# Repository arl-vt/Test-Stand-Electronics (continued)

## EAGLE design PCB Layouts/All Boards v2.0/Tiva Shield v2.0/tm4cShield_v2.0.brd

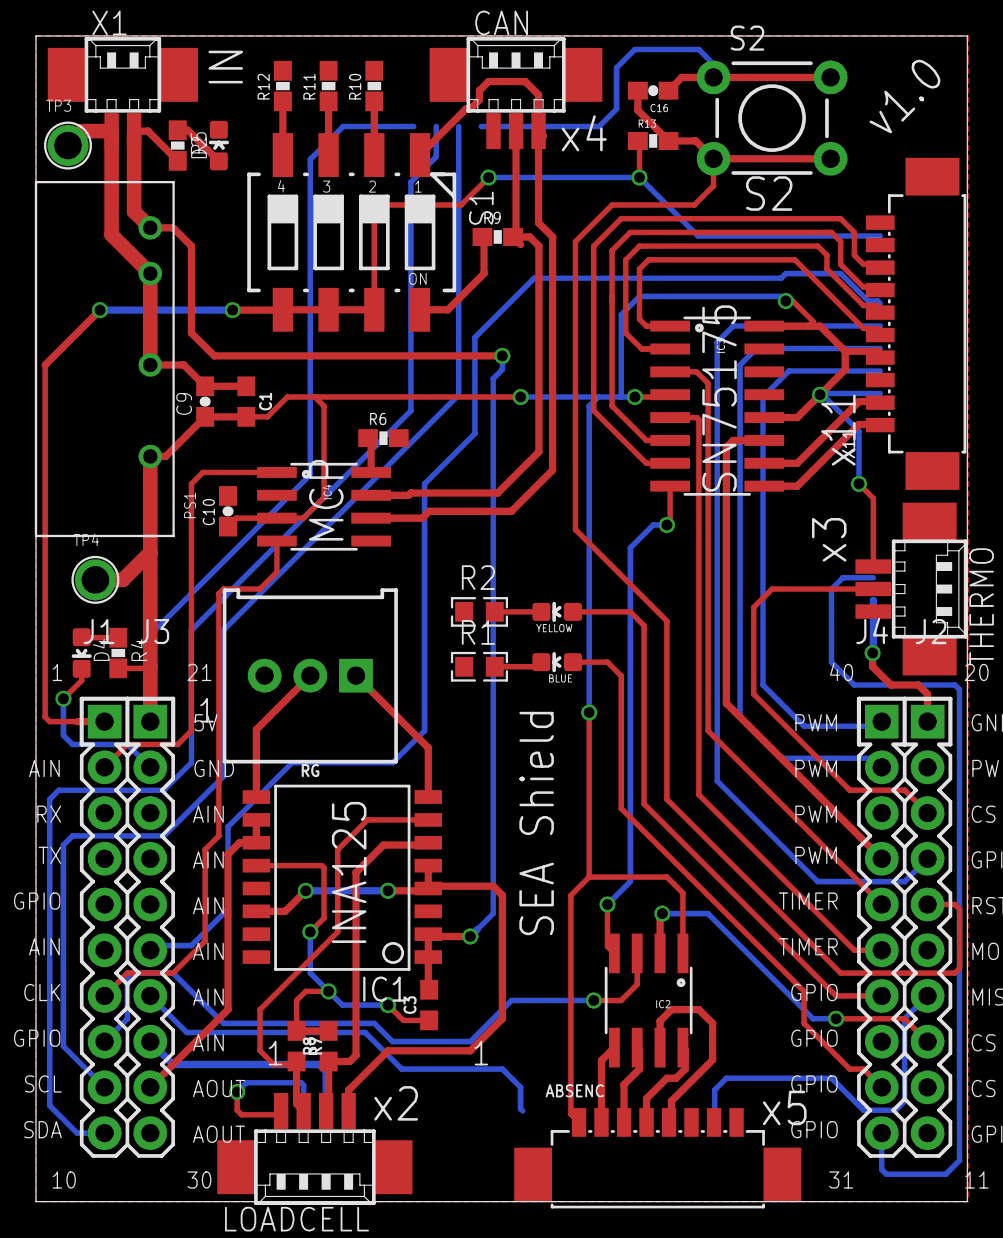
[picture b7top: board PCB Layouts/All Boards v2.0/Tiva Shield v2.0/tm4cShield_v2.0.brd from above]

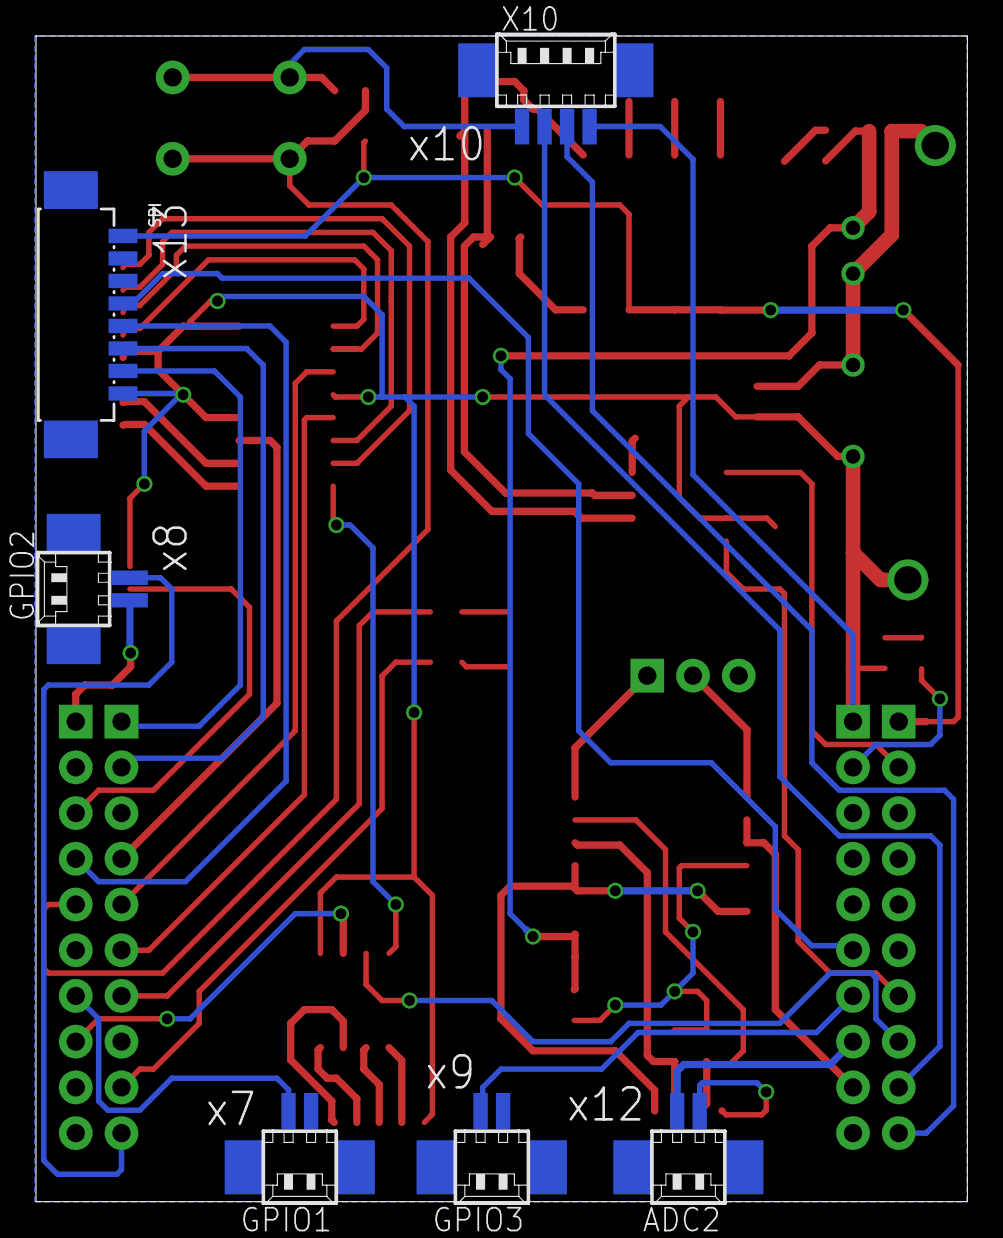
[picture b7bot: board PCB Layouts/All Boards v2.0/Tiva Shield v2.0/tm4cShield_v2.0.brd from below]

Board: 2 copper layers, 51.7 x 64.8 mm, 44 parts (6 on the bottom side), 52 nets.

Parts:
A1: 4X10-BOOSTERPACK
ABSENC: x5; PB-53261-08
ADC2: x12; 53261-02
BLUE: LED-0603
C1, C3: 0.1uF; 0603
C9: 2.2u; 0603-CAP
C10, C16: 100nF; 0603-CAP
CAN: x4; 53261-03
D2: 12V; LED-0603
D4: 5V; LED-0603
GPIO1: x7; 53261-02
GPIO2: x8; 53261-02
GPIO3: x9; 53261-02
IC1: INA125U; SO16-1
IC2: SP490; SOIC8
IC3: SN75175; SOIC16
IC4: MCP2551; SOIC8
LOADCELL: x2; 53261-04
PS1: 12/5; MURATA_NMG
R1, R2: RESC0603
R4: 1k; 0603-RES
R5: 4k7; 0603-RES
R6: 4.7K; 0603-RES
R7, R8: 10k; 0603
R9: 120; 0603-RES
R10, R11, R12, R13: 10K; 0603-RES
RG: 10k; TRIMPOT-PTH-3386U
S1: 219-04; CTS-219-04
S2: TACTILE-PTH
SPI: x13; PB-53261-08
THERMO: x3; 53261-03
TP3: GND; 5000_SERIES_TESTPOINT
TP4: 5V; 5000_SERIES_TESTPOINT
X1: x1; 53261-02
X10: I2C; 53261-04
X11: PB-53261-10
YELLOW: LED-0603

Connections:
3.3V: A1.1, R13.1, S1.5, S1.6, S1.7, SPI.1
5V: A1.21, ABSENC.1, C1.2, C9.1, C10.1, IC2.1, IC3.4, IC3.12, IC3.16, IC4.3, PS1.VOUT+, R4.2, SPI.8, THERMO.3, TP4.P$1, X10.1, X11.4
CAN_H: CAN.2, IC4.7, R9.2
CAN_L: CAN.1, IC4.6, S1.1
CH_A: IC3.2, X11.6
CH_A*: IC3.1, X11.5
CH_B: IC3.6, X11.7
CH_B*: IC3.7, X11.8
CH_I: IC3.10, X11.2
CH_I*: IC3.9, X11.1
CLOCK+: ABSENC.2, IC2.5
CLOCK-: ABSENC.3, IC2.6
DATA+: ABSENC.4, IC2.8
DATA-: ABSENC.5, IC2.7
GND: A1.20, A1.22, ABSENC.8, ADC2.2, C1.1, C3.1, C9.2, C10.2, C16.1, CAN.3, D2.C, D4.C, GPIO1.2, GPIO2.2, GPIO3.2, IC1.3, IC1.12, IC2.4, IC3.8, IC4.2, LOADCELL.1, PS1.VIN-, PS1.VOUT-, R1.1, R2.1, R6.2, R7.1, R8.2, R10.2, R11.2, R12.2, S2.1, S2.2, SPI.2, THERMO.1, TP3.P$1, X1.2, X10.4, X11.3
unnamed: D4.A, R4.1
unnamed: BLUE.C, R1.2
unnamed: IC1.8, RG.1
unnamed: R2.2, YELLOW.C
unnamed: IC1.9, RG.2
unnamed: R9.1, S1.8
unnamed: IC4.8, R6.1
unnamed: R10.1, S1.2
unnamed: R11.1, S1.3
unnamed: R12.1, S1.4
unnamed: D2.A, R5.1
PA4: A1.13, IC2.2
PA5: A1.8, IC2.3
PA6: A1.9, X10.3
PA7: A1.10, X10.2
PB4: A1.7, IC4.4
PB5: A1.2, IC4.1
PB6: A1.14, GPIO1.1
PC4: A1.37, IC3.11
PC5: A1.36, IC3.3
PC6: A1.35, IC3.5
PC7: A1.34, YELLOW.A
PD3: A1.26, SPI.4
PD7: A1.32, BLUE.A
PE0: A1.18, THERMO.2
PE1: A1.27, GPIO3.1
PE2: A1.28, ADC2.1
PE3: A1.29, IC1.10, IC1.11
PF0: A1.17, SPI.5
PF2: A1.40, SPI.7
PF3: A1.39, SPI.6
PF4: A1.31, GPIO2.1
RST: A1.16, C16.2, R13.2, S2.3, S2.4
V+: IC1.6, LOADCELL.3, R8.1
V-: IC1.7, LOADCELL.2, R7.2
VIN: C3.2, IC1.1, IC1.2, PS1.VIN+, R5.2, X1.1
V_2.5: IC1.4, IC1.5, IC1.14, LOADCELL.4

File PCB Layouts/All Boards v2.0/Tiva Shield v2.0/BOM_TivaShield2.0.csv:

Part/Designator,DigiKey,Quantity,Description,
Power,,,,
PS1,811-1706-5-ND,1,12V to 5V DC DC Converter,
C9,490-10733-2-ND,1,2.2uF capacitor 0603,
x1,WM7620TR-ND,1,2 pos picoblade,
C1,311-1341-2-ND,1,0.1uF capacitor 0603,
,,,,
Indication LED,,,,
D2,160-1447-1-ND,1,Red LED 0603,12V
D4,160-1435-2-ND,1,Green LED 0603,5V
R4,311-1.0KGRTR-ND,1,1k 0603 resistor,
R5,311-4.7KGRTR-ND,1,4k7 0603 resistor,
,,,,
Tiva Connector,,,,
Male header,952-1386-ND,2,10x2 male headers,
,,,,
Load Cell,,,,
x2,WM7622TR-ND,1,"4 pos picoblade, rt angle",
"R7, R8",311-10.0KHRTR-ND,2,"10Kohm resitor, 0603",
IC1,INA125U-ND,1,INA125U,
C3,311-1341-2-ND,`,0.1uF capacitor 0603,
RG,3266Y-1-103LF-ND,1,Trimming POT 10K,
,,,,
Thermocouple,,,,
x3,WM7621CT-ND,1,3 pos PICOblade conn,
,,,,
Absolute Encoders,,,,
IC2,1016-1830-1-ND,1,SP490 ,
x5,WM7626CT-ND,1,"8 pos, pico blade connector",
,,,,
Incremental Encoder,,,,
IC3,296-14954-2-ND,1,SN75175,
x11,WM7628TR-ND,1,10 pos pico blade,
,,,,
CAN,,,,
IC4,MCP2551-I/SN-ND,1,MCP2551,
x4,WM1754TR-ND,1,3 pos picoblade,
S1,CT2194LPST-ND,1,4 pos DIP switch,
R6,311-4.7KGRCT-ND,,"4.7k, 0603",
R9,P120GCT-ND,1,"120 ohm, 0603",
"R10, 11, 12",311-10.0KHRTR-ND,3,"10k, 0603",
C10,445-1316-2-ND,1,100nF,
,,,,
Reset,,,,
S2,SW793-ND,1,Reset switch,
C16,445-1316-2-ND,1,100nF Cap,
R13,311-10.0KHRTR-ND,,10K Resistor,
,,,,
Debug LED,,,,
LED1,475-2816-1-ND,1,Blue,
LED2,160-1448-1-ND,1,Yellow,
"R1, R2",311-4.7KGRTR-ND,2,"4k7, 0603",
,,,,
Additional ADC,,,,
x12,WM7620TR-ND,1,2 pos picoblade,
,,,,
Additional SPI,,,,
x13,WM7626CT-ND,1,"8 pos, pico blade",
,,,,
I2C,,,,
x10,WM7622TR-ND,1,4 pos Pico blade,
,,,,
GPIO,,,,
"x7, x8, x9",WM7620TR-ND,,2 pos picoblade,
,,,,
,,,,
,,,,
,,,,
,,,,
,,,,
,,,,
,,,,
,,,,
Female Components,,,,
PicoBlade 2 pos,WM1720-ND,2,"2 pos, picoblade","Power, ADC and GPIO additional"
PicoBlade 4 pos,WM1722-ND,1,"4 pos picoblade, female","Load cell , I2C"
Picoblade 3 pos,WM1721-ND,1,"3 pos, female","Thermocople, CAN"
PicoBlade 8 pos,WM1726-ND,1,"8 pos, female","Absolute Encoder, add SPI"
PicoBlade 10 pos,WM1728-ND,1,10 pos,Incremental Encoder

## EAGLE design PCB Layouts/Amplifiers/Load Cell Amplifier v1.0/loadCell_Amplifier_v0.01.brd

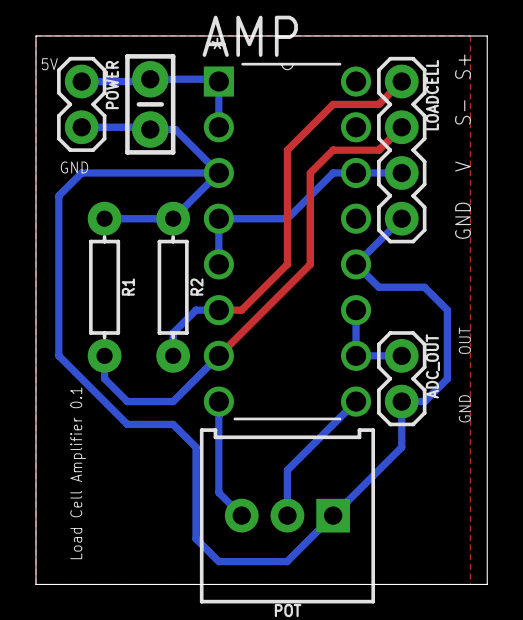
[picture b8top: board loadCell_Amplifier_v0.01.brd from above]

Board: 2 copper layers, 25.1 x 30.5 mm, 8 parts (0 on the bottom side), 8 nets.

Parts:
ADC_OUT: 1X02
AMP: INA125P; DIP254P762X508-16
C1: 0.1uF; CAP-PTH-SMALL-KIT
LOADCELL: 1X04
POT: 10k; TRIMPOT-PTH-3386U
POWER: 1X02
R1, R2: 10k; AXIAL-0.3

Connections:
5V: AMP.1, AMP.2, C1.1, POWER.1
GND: ADC_OUT.2, AMP.3, AMP.12, C1.2, LOADCELL.4, POT.1, POWER.2, R1.P$1, R2.P$1
OUT: ADC_OUT.1, AMP.10, AMP.11
RG: AMP.9, POT.2
RG_2: AMP.8, POT.3
S+: AMP.6, LOADCELL.1, R2.P$2
S-: AMP.7, LOADCELL.2, R1.P$2
V_REF: AMP.4, AMP.5, AMP.14, LOADCELL.3

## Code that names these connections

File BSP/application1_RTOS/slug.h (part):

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// J2.16 nothing (reset)
//--------------------------------------------------
// Internally connected on launchpad
// PD0 - PB6
// PD1 - PB7
//--------------------------------------------------
// Motors
// PB7 - Direction
// PF1 - PWM
// Current Monitor - PE5
//--------------------------------------------------
// Load Cells
// PE3
//--------------------------------------------------
// Thermocouple
// PE0
//--------------------------------------------------
// Absolute Encoders
// PA5 - Tx
// PA4 - Rx
//--------------------------------------------------
// Incremental Encoders
// PC5 - ChA
// PC6 - ChB
// PC4 - ChI
//--------------------------------------------------
// Display LEDS
// Blue - PD7
// Yellow - PC7
//--------------------------------------------------
// Reset Button
// RST
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// PA0, PA1
//--------------------------------------------------
// CAN
// PB5 - Tx
// PB4 - Rx
//--------------------------------------------------
// Additional ADC
// PE2
//--------------------------------------------------
// Additional SPI
// PF0 - Rx
// PF2 - CLK
// PF3 - CS
// PD3 - TX
//--------------------------------------------------
// I2C
// PA6 - SCL
// PA7 - SDA
//--------------------------------------------------
// GPIO
// PB6, PF4, PE1
//--------------------------------------------------

// ************* includes ******************************************
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// *************** LEDs and Buttons ***********************
// ********************************************************
// ----------------BlueLED_Init-----------------------
// Initializes the Blue LED on PD7
// Input: None
// Output: None
void BlueLED_Init(void);
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void BlueLED_Toggle(void);

// ----------------YellowLED_Init-----------------------
// Initializes the Yellow LED on PC7
// Input: None
// Output: None
void YellowLED_Init(void);
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void YellowLED_Toggle(void);

// ---------------Button1_Init----------------------
// Initializes the GPIO pin for the button PF4 (J2.17) as input.
// Input: none
// Output: none
void Button1_Init(void);
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uint8_t Button1_Input(void);

// ----------------RGBled_Init-----------------------
// Initializes the RGB LED on PF1, PF2 and PF3
void RGBled_Init(uint8_t red, uint8_t green, uint8_t blue);

// ----------------RGBled_Set-----------------------
// Sets the RGB LED on PF1, PF2 and PF3
// Input: non zero input sents the LEDs
// Output: None
void RGBled_Set(uint8_t red, uint8_t green, uint8_t blue);

// ----------------RGBled_Toggle-----------------------
// Toggles the RGB LED on PF1, PF2 and PF3
// Input: non zero input toggles the LEDs
//         red is toggle for red
//         blue is toggle for blue
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double getMotorPWMPeriod(void);

//------------------setDirection()---------------------------
//Set Direction Pin High
//Input: None
//Output: None
void setDirection(void);

//------------------clearDirection()---------------------------
//Clear Direction Pin Low
//Input: None
//Output: None
void clearDirection(void);
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
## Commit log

2017-04-13 Added Senior Design AMC shield
2017-04-13 Added Motor shiel v1.0 with minifit connectors
2017-04-13 added previous tiva board anf load cell amplifier board
2017-04-13 added eagle libraries
2017-04-29 Add files via upload
    Ryan's modified Motor Shield boards.
2017-05-03 added datasheets
2017-05-06 Rename Boards/Motor Drivers/motor_shield__SD_v1.1 - Ryan.brd to Boards/Motor Drivers/Ryan-s Motor Shield Versions/motor_shield__SD_v1.1 - Ryan.brd
2017-05-06 Rename Boards/Motor Drivers/motor_shield__SD_v1.1 - Ryan.sch to Boards/Motor Drivers/Ryan-s Motor Shield Versions/motor_shield__SD_v1.1 - Ryan.sch
2017-05-09 Changes tiva headers, corrected ground and vol connections, layout finalizing. started routing
2017-05-09 added bill of materia
2017-05-09 Completed Routing
2017-05-18 Added BSP
    GPIO, Motor
2017-05-19 Added revision to the motor board
2017-06-12 Added Force Control and BSP for related peripherals
2017-06-13 Testing force control PID
2017-06-14 load cell in force unit
2017-06-14 Force control working on THOR with jitter
2017-06-18 Tiva board
2017-06-19 Tiva shield
2017-06-21 RTOS clock
2017-06-22 Final Amplifier, tiva shield and servo shield
    updates eagle libraries
2017-06-22 BSP tested led, tiva led and buton, timers, logger and console
2017-06-22 BSP logger
2017-06-24 BSP tested temp sensor
2017-06-24 controller tested feedforward
2017-06-26 cleaning up
2017-07-03 MRAC adaptive control
2017-07-03 incremental encoder
